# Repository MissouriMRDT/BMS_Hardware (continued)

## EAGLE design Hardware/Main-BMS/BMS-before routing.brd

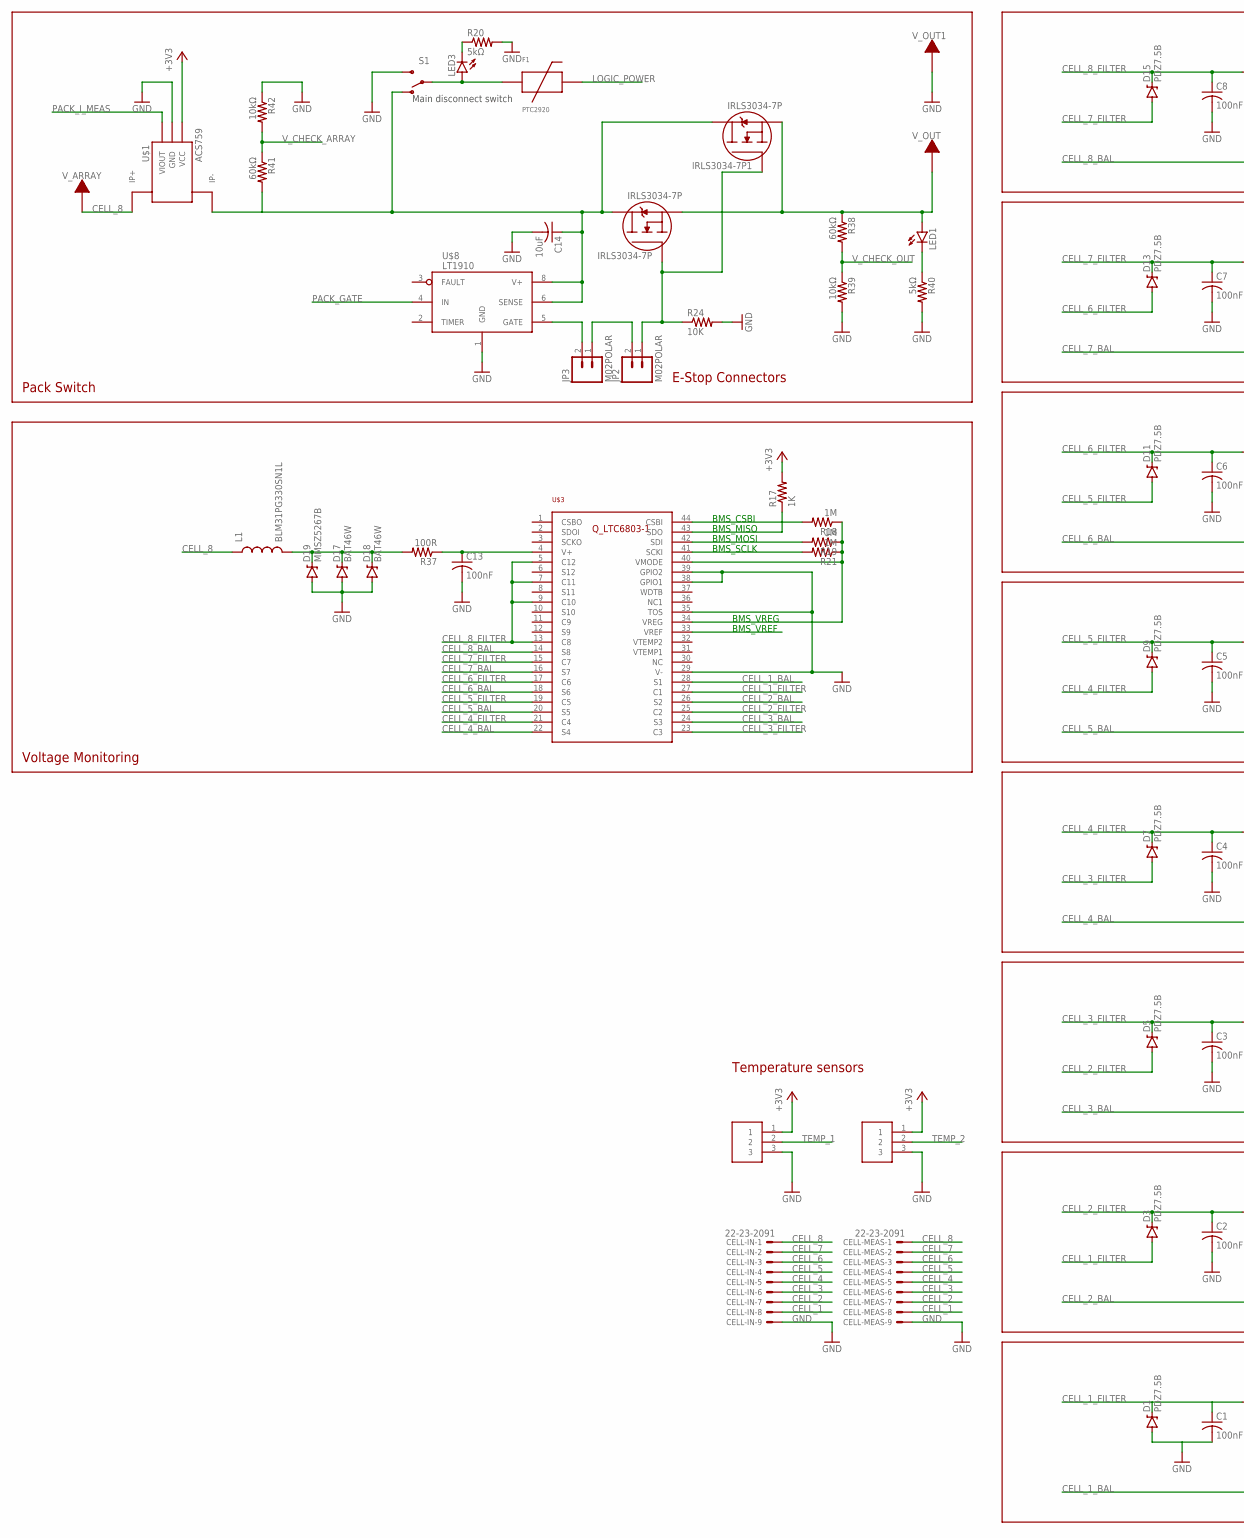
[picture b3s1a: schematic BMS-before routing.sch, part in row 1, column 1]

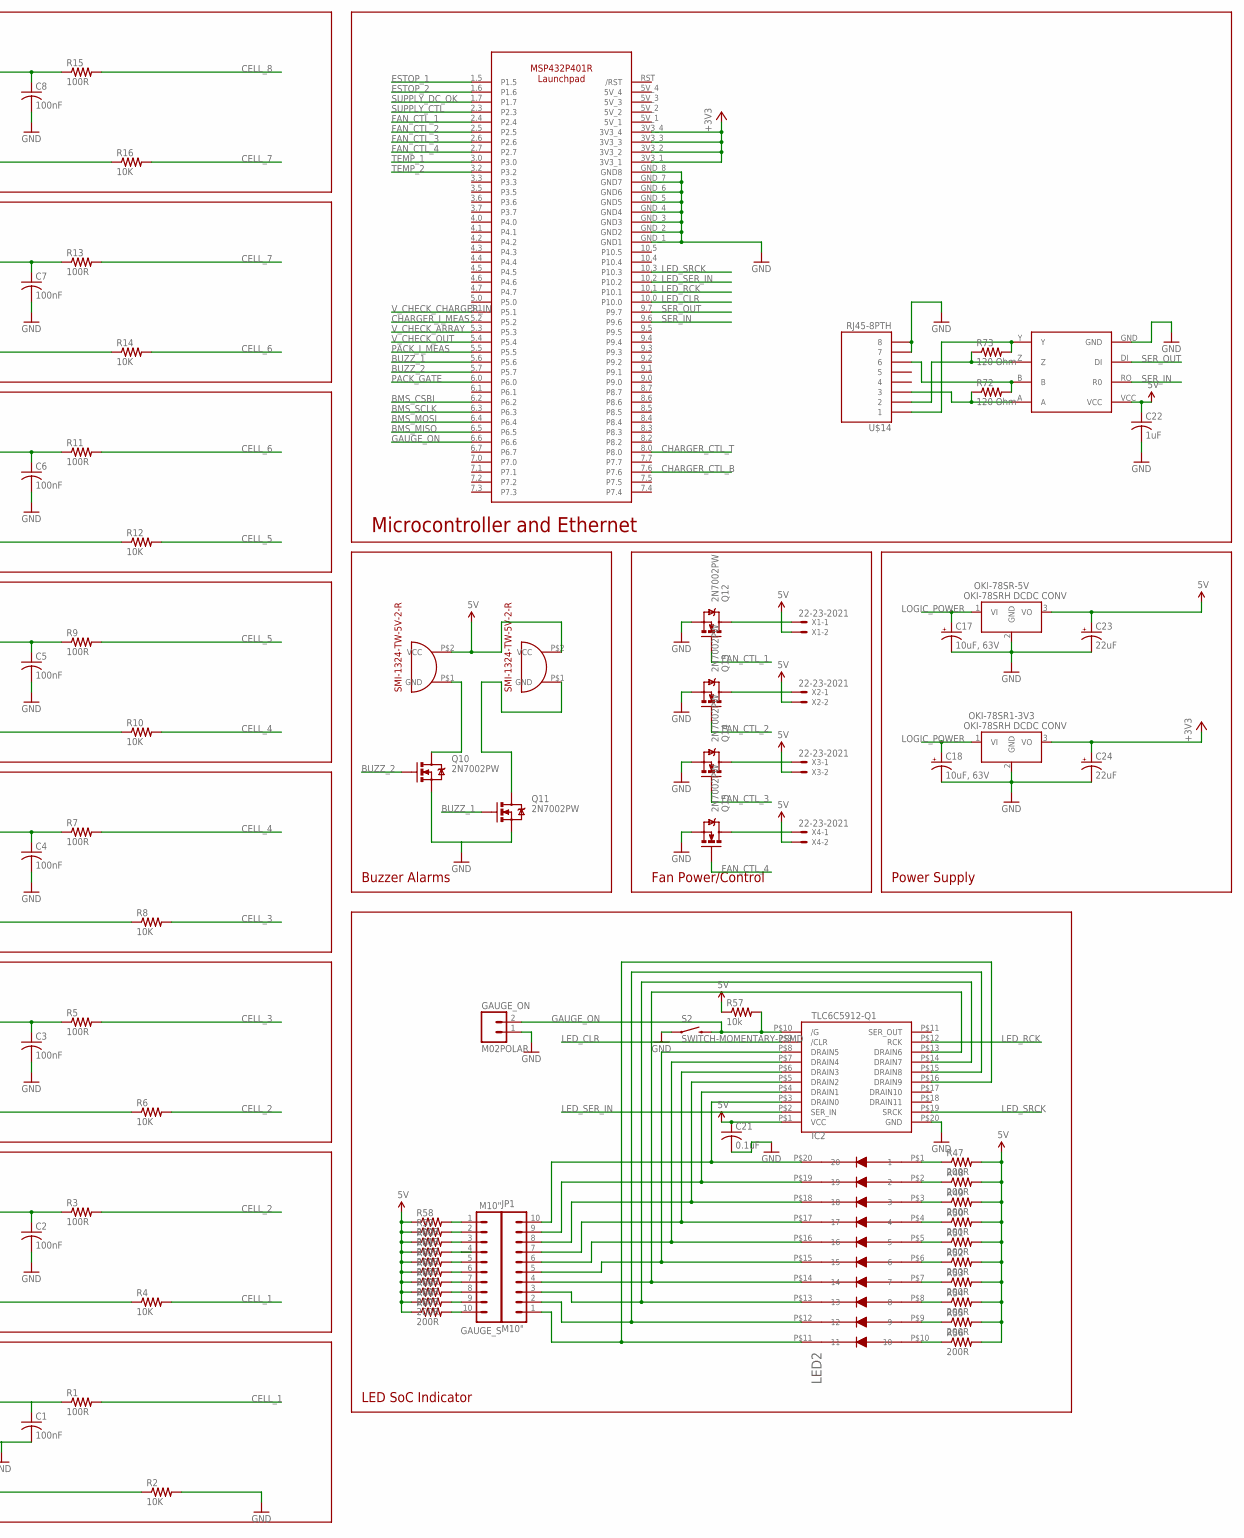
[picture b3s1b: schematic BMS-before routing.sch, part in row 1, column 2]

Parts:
C1, C2, C3, C4, C5, C6, C7, C8, C13: 100nF; C1206
C14: 10uF; C1206
C17, C18: 10uF, 63V; PANASONIC_D
C21: 0.1uF; C1206
C22: 1uF; C1206
C23, C24: 22uF; PANASONIC_D
CELL-IN: 22-23-2091
CELL-MEAS: 22-23-2091
D1, D3, D5, D7, D9, D11, D13, D15: PDZ7.5B; SOD-323
D17, D18: BAT46W; SOD-123
D19: MMSZ5267B; SOD-123
F1: PTC2920; 2920
GAUGE_ON: M02POLAR; MOLEX-1X2
GAUGE_S: M10"; 1X10
IC2: TLC6C5912-Q1; SOIC-20
IRLS3034-7P, IRLS3034-7P1: IRLS3034-7P; D2PAK-7
J1, J2: SL03THROUGH_HOLE; MOLEX_SL_03_THROUGH_HOLE
JP1: M10"; 1X10
JP2, JP3: M02POLAR; MOLEX-1X2
L1: BLM31PG330SN1L; 1210
LED1, LED3: LED1206; LED-1206
LED2: LED-DC7G3HWA; LED-10
OKI-78SR1-3V3: Q_OKI-78SR12; OKI-78SRH
OKI-78SR-5V: Q_OKI-78SR5; OKI-78SRH
Q10, Q11, Q12, Q13, Q14, Q15: 2N7002PW; SOT323
R1, R3, R5, R7, R9, R11, R13, R15, R37: 100R; R1206
R2, R4, R6, R8, R10, R12, R14, R16, R24: 10K; 0603-RES
R17: 1K; 0603-RES
R18, R19, R21: 1M; R1206
R20, R40: 5kΩ; R1206
R38, R41: 60kΩ; R1206
R39, R42: 10kΩ; R1206
R47, R48, R49, R50, R51, R52, R53, R54, R55, R56, R58, R59, R60, R61, R62, R63, R64, R65, R66, R67: 200R; R1206
R57: 10k; R1206
R72, R73: 120 Ohm; 1206
S1: SWITCH-SPDTPTH; SWITCH-SPDT
S2: SWITCH-MOMENTARY-2SMD; TACTILE-SWITCH-SMD
U$1: ACS759; PFF_LEADFORM
U$2, U$4: SMI-1324-TW-5V-2-R
U$3: Q_LTC6803-1; SSOP44
U$8: LT1910; SO8
U$13: MSP432P401R-LAUNCHPAD
U$14: RJ45-8PTH; RJ45-8
U$15: MAX3077; MAX3070E
V_ARRAY: TERMINAL_HOLE; LARGE_TERMINAL_HOLE
V_OUT, V_OUT1: TERMINAL_HOLE; LARGE_TERMINAL_HOLE
X1, X2, X3, X4: 22-23-2021

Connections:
5V: C21.1, C22.1, C23.+, IC2.P$1 (VCC), OKI-78SR-5V.3 (VO), R47.2, R48.2, R49.2, R50.2, R51.2, R52.2, R53.2, R54.2, R55.2, R56.2, R57.1, R58.1, R59.1, R60.1, R61.1, R62.1, R63.1, R64.1, R65.1, R66.1, R67.1, U$2.P$2 (VCC), U$4.P$2 (VCC), U$15.VCC, X1.2, X2.2, X3.2, X4.2
+3V3: C24.+, J1.1, J2.1, OKI-78SR1-3V3.3 (VO), R17.2, U$1.1 (VCC), U$13.3V3_1, U$13.3V3_2, U$13.3V3_3, U$13.3V3_4
BMS_CSBI: R18.2, U$3.44 (CSBI), U$13.6.2
BMS_MISO: R17.1, U$3.43 (SDO), U$13.6.5
BMS_MOSI: R19.2, U$3.42 (SDI), U$13.6.4
BMS_SCLK: R21.2, U$3.41 (SCKI), U$13.6.3
BMS_VREF: U$3.33 (VREF)
BMS_VREG: R18.1, R19.1, R21.1, U$3.34 (VREG), U$3.40 (VMODE)
BUZZ_1: Q11.1 (G), U$13.5.6
BUZZ_2: Q10.1 (G), U$13.5.7
CELL_1: CELL-IN.8, CELL-MEAS.8, R1.2, R4.2
CELL_1_BAL: R2.1, U$3.28 (S1)
CELL_1_FILTER: C1.1, D1.C, D3.A, R1.1, U$3.27 (C1)
CELL_2: CELL-IN.7, CELL-MEAS.7, R3.2, R6.2
CELL_2_BAL: R4.1, U$3.26 (S2)
CELL_2_FILTER: C2.1, D3.C, D5.A, R3.1, U$3.25 (C2)
CELL_3: CELL-IN.6, CELL-MEAS.6, R5.2, R8.2
CELL_3_BAL: R6.1, U$3.24 (S3)
CELL_3_FILTER: C3.1, D5.C, D7.A, R5.1, U$3.23 (C3)
CELL_4: CELL-IN.5, CELL-MEAS.5, R7.2, R10.2
CELL_4_BAL: R8.1, U$3.22 (S4)
CELL_4_FILTER: C4.1, D7.C, D9.A, R7.1, U$3.21 (C4)
CELL_5: CELL-IN.4, CELL-MEAS.4, R9.2, R12.2
CELL_5_BAL: R10.1, U$3.20 (S5)
CELL_5_FILTER: C5.1, D9.C, D11.A, R9.1, U$3.19 (C5)
CELL_6: CELL-IN.3, CELL-MEAS.3, R11.2, R14.2
CELL_6_BAL: R12.1, U$3.18 (S6)
CELL_6_FILTER: C6.1, D11.C, D13.A, R11.1, U$3.17 (C6)
CELL_7: CELL-IN.2, CELL-MEAS.2, R13.2, R16.2
CELL_7_BAL: R14.1, U$3.16 (S7)
CELL_7_FILTER: C7.1, D13.C, D15.A, R13.1, U$3.15 (C7)
CELL_8: CELL-IN.1, CELL-MEAS.1, L1.1, R15.2, U$1.4_1 (IP+), U$1.4_2 (IP+), U$1.4_3 (IP+), U$1.4_4 (IP+), U$1.4_5 (IP+), U$1.4_6 (IP+), U$1.4_7 (IP+), U$1.4_8 (IP+), U$1.4_9 (IP+), U$1.4_10 (IP+), U$1.4_11 (IP+), U$1.4_12 (IP+), U$1.4_13 (IP+), U$1.4_14 (IP+), U$1.4_15 (IP+), U$1.4_16 (IP+), U$1.4_B (IP+), V_ARRAY.P$1
CELL_8_BAL: R16.1, U$3.14 (S8)
CELL_8_FILTER: C8.1, D15.C, R15.1, U$3.5 (C12), U$3.7 (C11), U$3.9 (C10), U$3.13 (C8)
CHARGER_CTL_B: U$13.7.6
CHARGER_CTL_T: U$13.8.0
CHARGER_I_MEAS: U$13.5.2
ESTOP_1: U$13.1.5
ESTOP_2: U$13.1.6
FAN_CTL_1: Q12.1 (G), U$13.2.4
FAN_CTL_2: Q13.1 (G), U$13.2.5
FAN_CTL_3: Q14.1 (G), U$13.2.6
FAN_CTL_4: Q15.1 (G), U$13.2.7
GAUGE_D: IC2.P$6 (DRAIN3), JP1.7, LED2.P$17 (17)
GAUGE_ON: GAUGE_ON.2, IC2.P$10 (/G), R57.2, S2.3 (2), U$13.6.6
GND: C1.2, C2.2, C3.2, C4.2, C5.2, C6.2, C7.2, C8.2, C13.2, C14.2, C17.-, C18.-, C21.2, C22.2, C23.-, C24.-, CELL-IN.9, CELL-MEAS.9, D1.A, D17.A, D18.A, D19.A, GAUGE_ON.1, IC2.P$20 (GND), J1.3, J2.3, OKI-78SR1-3V3.2 (GND), OKI-78SR-5V.2 (GND), Q10.2 (S), Q11.2 (S), Q12.2 (S), Q13.2 (S), Q14.2 (S), Q15.2 (S), R2.2, R20.2, R24.2, R39.2, R40.2, R42.1, S1.3 (S), S2.1, U$1.2 (GND), U$3.29 (V-), U$3.35 (TOS), U$3.38 (GPIO1), U$3.39 (GPIO2), U$8.1 (GND), U$13.GND_1 (GND1), U$13.GND_2 (GND2), U$13.GND_3 (GND3), U$13.GND_4 (GND4), U$13.GND_5 (GND5), U$13.GND_6 (GND6), U$13.GND_7 (GND7), U$13.GND_8 (GND8), U$14.7, U$14.8, U$15.GND, V_OUT1.P$1
LED_CLR: IC2.P$9 (/CLR), U$13.10.0
LED_RCK: IC2.P$12 (RCK), U$13.10.1
LED_SER_IN: IC2.P$2 (SER_IN), U$13.10.2
LED_SRCK: IC2.P$19 (SRCK), U$13.10.3
LOGIC_POWER: C17.+, C18.+, F1.P$2, OKI-78SR1-3V3.1 (VI), OKI-78SR-5V.1 (VI)
unnamed: JP3.2, U$8.5 (GATE)
unnamed: F1.P$1, LED3.A, S1.2
unnamed: IRLS3034-7P.2 (SOURCE), IRLS3034-7P.3 (SOURCE), IRLS3034-7P.4 (SOURCE), IRLS3034-7P.5 (SOURCE), IRLS3034-7P.6 (SOURCE), IRLS3034-7P1.2 (SOURCE), IRLS3034-7P1.3 (SOURCE), IRLS3034-7P1.4 (SOURCE), IRLS3034-7P1.5 (SOURCE), IRLS3034-7P1.6 (SOURCE), LED1.A, R38.1, V_OUT.P$1
unnamed: LED3.C, R20.1
unnamed: JP2.2, JP3.1
unnamed: D17.C, D18.C, D19.C, L1.2, R37.2
unnamed: C13.1, R37.1, U$3.4 (V+)
unnamed: IC2.P$3 (DRAIN0), JP1.10, LED2.P$20 (20)
unnamed: IRLS3034-7P.1 (GATE), IRLS3034-7P1.1 (GATE), JP2.1, R24.1
unnamed: R73.2, U$14.1, U$15.Y
unnamed: LED1.C, R40.1
unnamed: C14.1, IRLS3034-7P.PAD (DRAIN), IRLS3034-7P1.PAD (DRAIN), R41.2, S1.1 (O), U$1.5_1 (IP-), U$1.5_2 (IP-), U$1.5_3 (IP-), U$1.5_4 (IP-), U$1.5_5 (IP-), U$1.5_6 (IP-), U$1.5_7 (IP-), U$1.5_8 (IP-), U$1.5_9 (IP-), U$1.5_10 (IP-), U$1.5_11 (IP-), U$1.5_12 (IP-), U$1.5_13 (IP-), U$1.5_14 (IP-), U$1.5_15 (IP-), U$1.5_16 (IP-), U$1.5_B (IP-), U$1.5_T (IP-), U$8.6 (SENSE), U$8.8 (V+)
unnamed: IC2.P$4 (DRAIN1), JP1.9, LED2.P$19 (19)
unnamed: IC2.P$5 (DRAIN2), JP1.8, LED2.P$18 (18)
unnamed: R73.1, U$14.2, U$15.Z
unnamed: IC2.P$7 (DRAIN4), JP1.6, LED2.P$16 (16)
unnamed: IC2.P$8 (DRAIN5), JP1.5, LED2.P$15 (15)
unnamed: IC2.P$13 (DRAIN6), JP1.4, LED2.P$14 (14)
unnamed: IC2.P$14 (DRAIN7), JP1.3, LED2.P$13 (13)
unnamed: IC2.P$15 (DRAIN8), JP1.2, LED2.P$12 (12)
unnamed: IC2.P$16 (DRAIN9), JP1.1, LED2.P$11 (11)
unnamed: LED2.P$1 (1), R47.1
unnamed: LED2.P$2 (2), R48.1
unnamed: LED2.P$3 (3), R49.1
unnamed: LED2.P$4 (4), R50.1
unnamed: LED2.P$5 (5), R51.1
unnamed: LED2.P$6 (6), R52.1
unnamed: LED2.P$7 (7), R53.1
unnamed: LED2.P$8 (8), R54.1
unnamed: LED2.P$9 (9), R55.1
unnamed: LED2.P$10 (10), R56.1
unnamed: R72.2, U$14.6, U$15.B
unnamed: Q11.3 (D), U$4.P$1 (GND)
unnamed: Q10.3 (D), U$2.P$1 (GND)
unnamed: Q12.3 (D), X1.1
unnamed: R72.1, U$14.3, U$15.A
unnamed: Q13.3 (D), X2.1
unnamed: Q14.3 (D), X3.1
unnamed: Q15.3 (D), X4.1
unnamed: GAUGE_S.1, R58.2
unnamed: GAUGE_S.2, R59.2
unnamed: GAUGE_S.3, R60.2
unnamed: GAUGE_S.4, R61.2
unnamed: GAUGE_S.5, R62.2
unnamed: GAUGE_S.6, R63.2
unnamed: GAUGE_S.7, R64.2
unnamed: GAUGE_S.8, R65.2
unnamed: GAUGE_S.9, R66.2
unnamed: GAUGE_S.10, R67.2
PACK_GATE: U$8.4 (IN), U$13.6.0
PACK_I_MEAS: U$1.3 (VIOUT), U$13.5.5
SER_IN: U$13.9.6, U$15.RO (R0)
SER_OUT: U$13.9.7, U$15.DI
SUPPLY_CTL: U$13.2.3
SUPPLY_DC_OK: U$13.1.7
TEMP_1: J2.2, U$13.3.0
TEMP_2: J1.2, U$13.3.2
V_CHECK_ARRAY: R41.1, R42.2, U$13.5.3
V_CHECK_CHARGER_IN: U$13.5.1
V_CHECK_OUT: R38.2, R39.1, U$13.5.4

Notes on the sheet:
Pack Switch
Main disconnect switch
E-Stop Connectors
Power Supply
LED SoC Indicator
Buzzer Alarms
Fan Power/Control
Microcontroller and Ethernet
CELL_8_FILTER
CELL_7_FILTER
CELL_6_FILTER
CELL_5_FILTER
CELL_4_FILTER
CELL_4_BAL
CELL_5_BAL
CELL_6_BAL
CELL_7_BAL
CELL_8_BAL
CELL_1_BAL
CELL_1_FILTER
CELL_1
CELL_2_BAL
CELL_3_FILTER
CELL_2_FILTER
CELL_3_BAL
BMS_VREG
BMS_VREF
BMS_CSBI
BMS_MISO
BMS_MOSI
BMS_SCLK
Voltage Monitoring
Temperature sensors

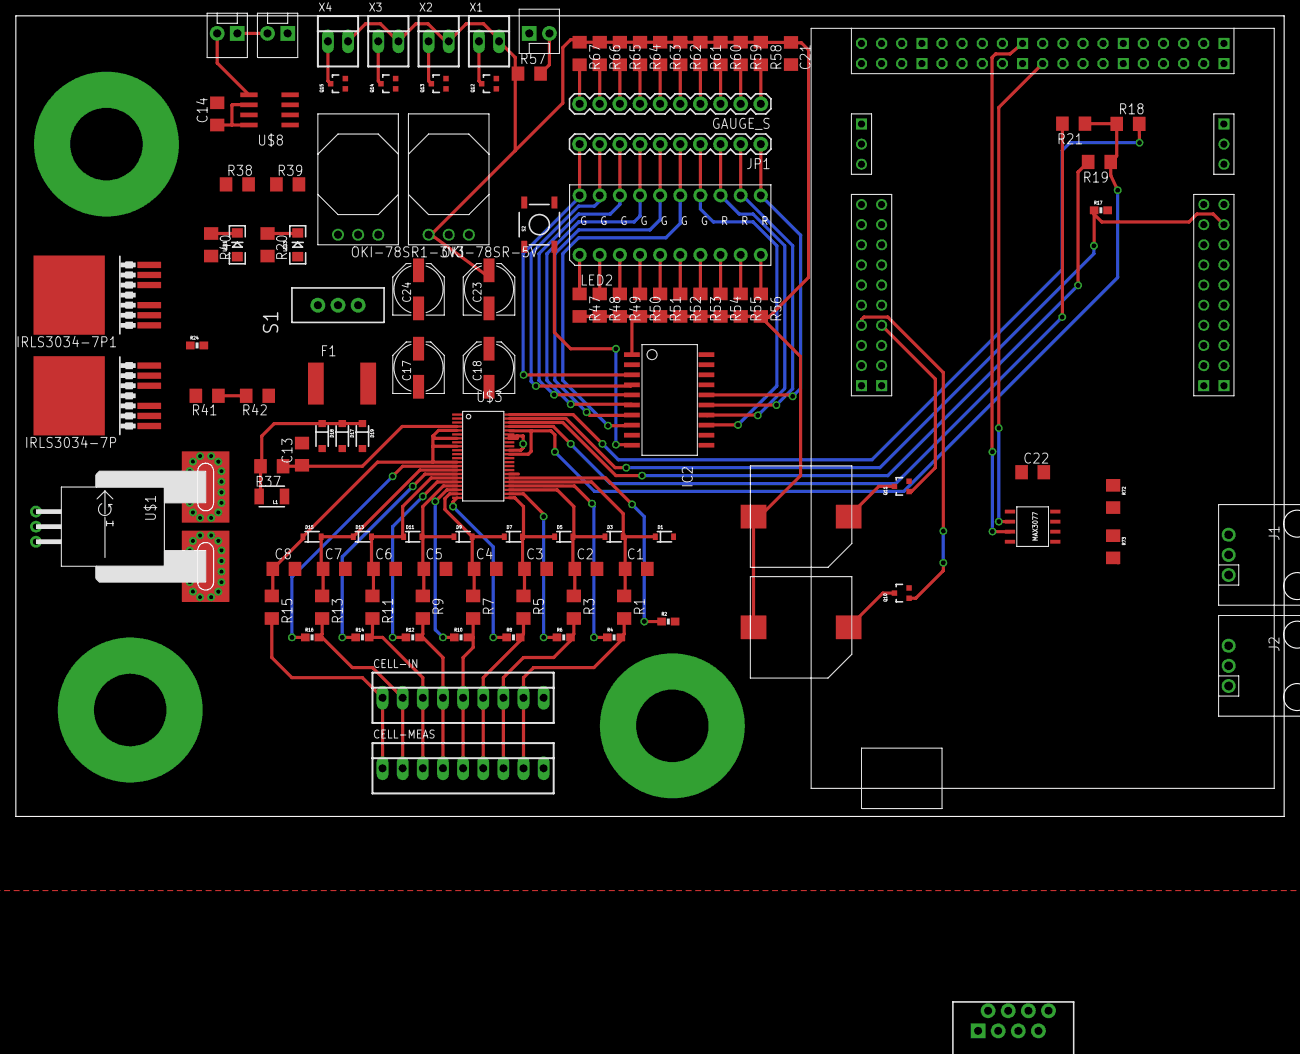
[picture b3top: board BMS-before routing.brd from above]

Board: 2 copper layers, 160.0 x 101.0 mm, 120 parts (0 on the bottom side), 102 nets.

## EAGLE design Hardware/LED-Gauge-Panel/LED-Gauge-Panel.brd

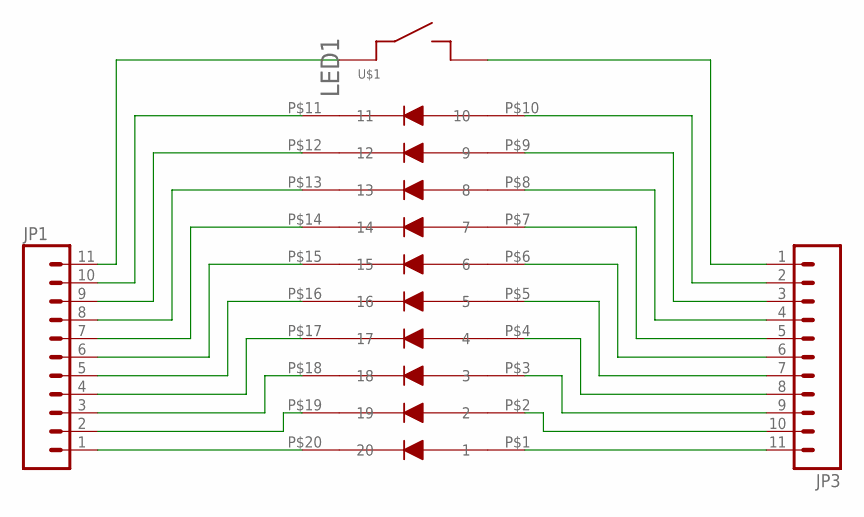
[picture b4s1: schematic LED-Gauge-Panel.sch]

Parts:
JP1, JP3: M11PTH; 1X11
LED1: LED-DC7G3HWA; LED-10
U$1: MOMENTARY-SWITCH-EVQ1; EVQ11

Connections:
unnamed: JP1.1, LED1.P$20 (20)
unnamed: JP1.2, LED1.P$19 (19)
unnamed: JP1.3, LED1.P$18 (18)
unnamed: JP1.4, LED1.P$17 (17)
unnamed: JP1.5, LED1.P$16 (16)
unnamed: JP1.6, LED1.P$15 (15)
unnamed: JP1.7, LED1.P$14 (14)
unnamed: JP1.8, LED1.P$13 (13)
unnamed: JP1.9, LED1.P$12 (12)
unnamed: JP1.10, LED1.P$11 (11)
unnamed: JP3.11, LED1.P$1 (1)
unnamed: JP3.10, LED1.P$2 (2)
unnamed: JP3.9, LED1.P$3 (3)
unnamed: JP3.8, LED1.P$4 (4)
unnamed: JP3.7, LED1.P$5 (5)
unnamed: JP3.6, LED1.P$6 (6)
unnamed: JP3.5, LED1.P$7 (7)
unnamed: JP3.4, LED1.P$8 (8)
unnamed: JP3.3, LED1.P$9 (9)
unnamed: JP3.2, LED1.P$10 (10)
unnamed: JP1.11, U$1.P$1
unnamed: JP3.1, U$1.P$2

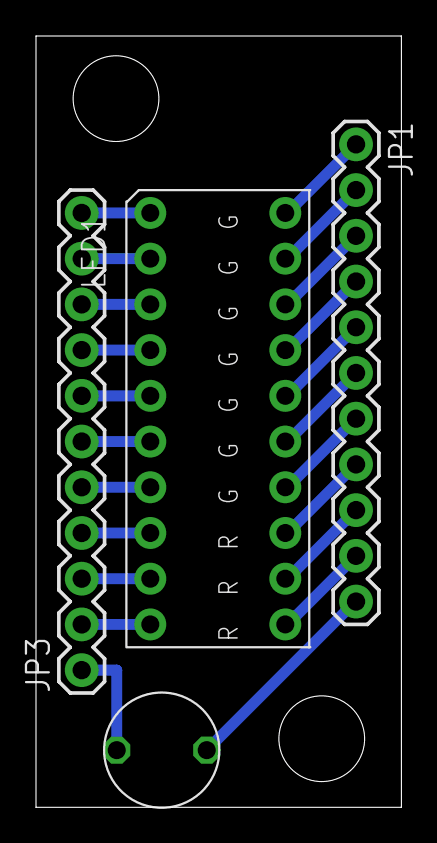
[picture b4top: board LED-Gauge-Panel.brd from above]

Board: 2 copper layers, 20.3 x 42.9 mm, 4 parts (0 on the bottom side), 22 nets.

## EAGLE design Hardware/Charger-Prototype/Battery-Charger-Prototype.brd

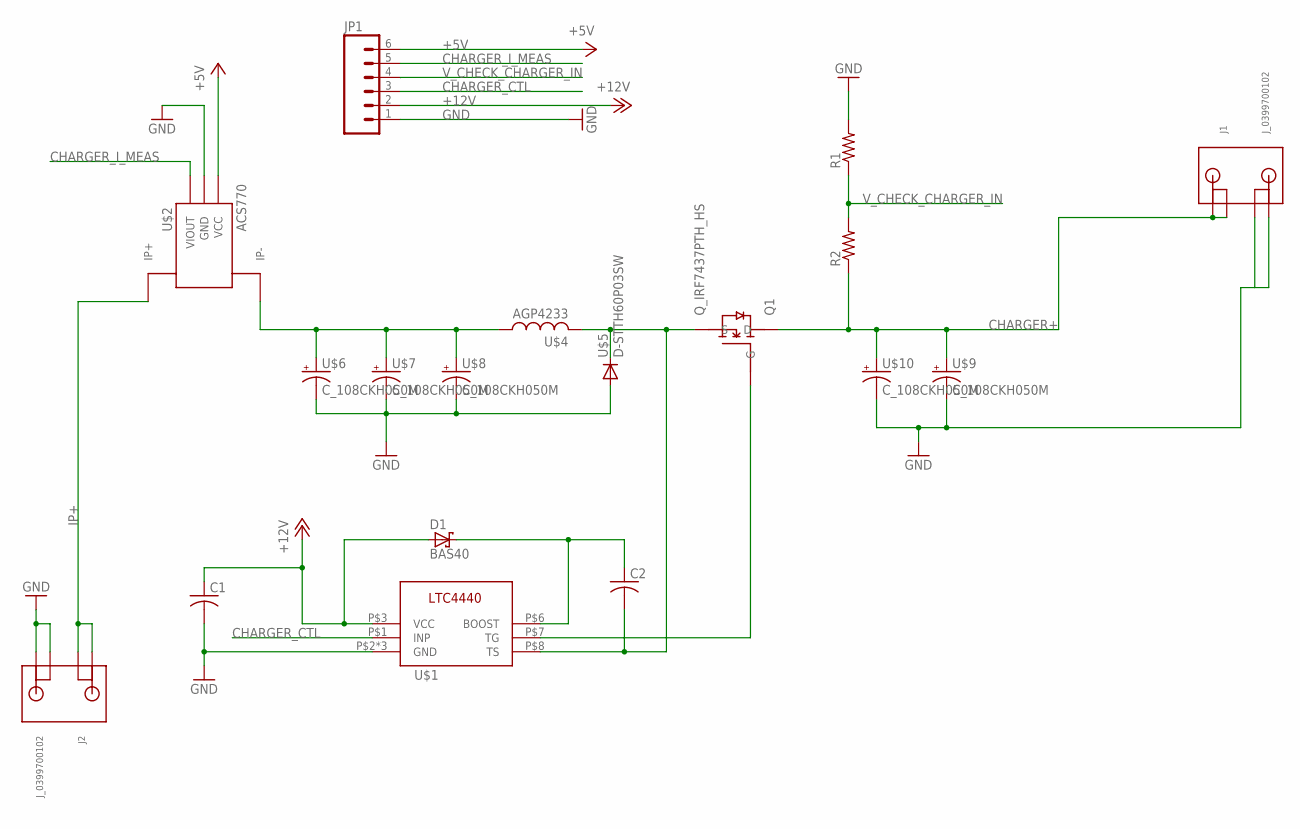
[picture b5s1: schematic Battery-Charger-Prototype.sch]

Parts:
C1, C2: C-USC1206; C1206
D1: BAS40; SOT23
J1, J2: J_0399700102; J_2CONHC
JP1: M06SILK_FEMALE_PTH; 1X06
Q1: Q_IRF7437PTH_HS; TO-220-531102B02500G
R1, R2: R-US_R1206; R1206
U$1: LTC4440; MS8E
U$2: ACS770; PFF_LEADFORM
U$4: AGP4233
U$5: D-STTH60P03SW; TO-247-VERT
U$6, U$7, U$8, U$9, U$10: C_108CKH050M; C_16MM

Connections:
+5V: JP1.6, U$2.1 (VCC)
+12V: C1.1, D1.1 (A), JP1.2, U$1.P$3 (VCC)
CHARGER+: J1.PIN1-1 (1-1), J1.PIN1-2 (1-2), Q1.2 (D), R2.1, U$9.+, U$10.+
CHARGER_CTL: JP1.3, U$1.P$1 (INP)
CHARGER_I_MEAS: JP1.5, U$2.3 (VIOUT)
GND: C1.2, J1.PIN2-1 (2-1), J1.PIN2-2 (2-2), J2.PIN2-1 (2-1), J2.PIN2-2 (2-2), JP1.1, R1.2, U$1.P$2 (GND), U$1.P$4 (GND), U$1.P$9 (GND), U$2.2 (GND), U$5.P$1 (A), U$5.P$3 (A), U$6.GND (-), U$7.GND (-), U$8.GND (-), U$9.GND (-), U$10.GND (-)
IP+: J2.PIN1-1 (1-1), J2.PIN1-2 (1-2), U$2.4_1 (IP+), U$2.4_2 (IP+), U$2.4_3 (IP+), U$2.4_4 (IP+), U$2.4_5 (IP+), U$2.4_6 (IP+), U$2.4_7 (IP+), U$2.4_8 (IP+), U$2.4_9 (IP+), U$2.4_10 (IP+), U$2.4_11 (IP+), U$2.4_12 (IP+), U$2.4_13 (IP+), U$2.4_14 (IP+), U$2.4_15 (IP+), U$2.4_16 (IP+), U$2.4_B (IP+), U$2.4_T (IP+)
IP-: U$2.5_1 (IP-), U$2.5_2 (IP-), U$2.5_3 (IP-), U$2.5_4 (IP-), U$2.5_5 (IP-), U$2.5_6 (IP-), U$2.5_7 (IP-), U$2.5_8 (IP-), U$2.5_9 (IP-), U$2.5_10 (IP-), U$2.5_11 (IP-), U$2.5_12 (IP-), U$2.5_13 (IP-), U$2.5_14 (IP-), U$2.5_15 (IP-), U$2.5_16 (IP-), U$2.5_B (IP-), U$2.5_T (IP-), U$4.P$1 (1), U$6.+, U$7.+, U$8.+
MOS_OUT: C2.2, Q1.3 (S), U$1.P$8 (TS), U$4.P$2 (2), U$5.P$2 (C)
unnamed: C2.1, D1.3 (C), U$1.P$6 (BOOST)
unnamed: Q1.1 (G), U$1.P$7 (TG)
V_CHECK_CHARGER_IN: JP1.4, R1.1, R2.2

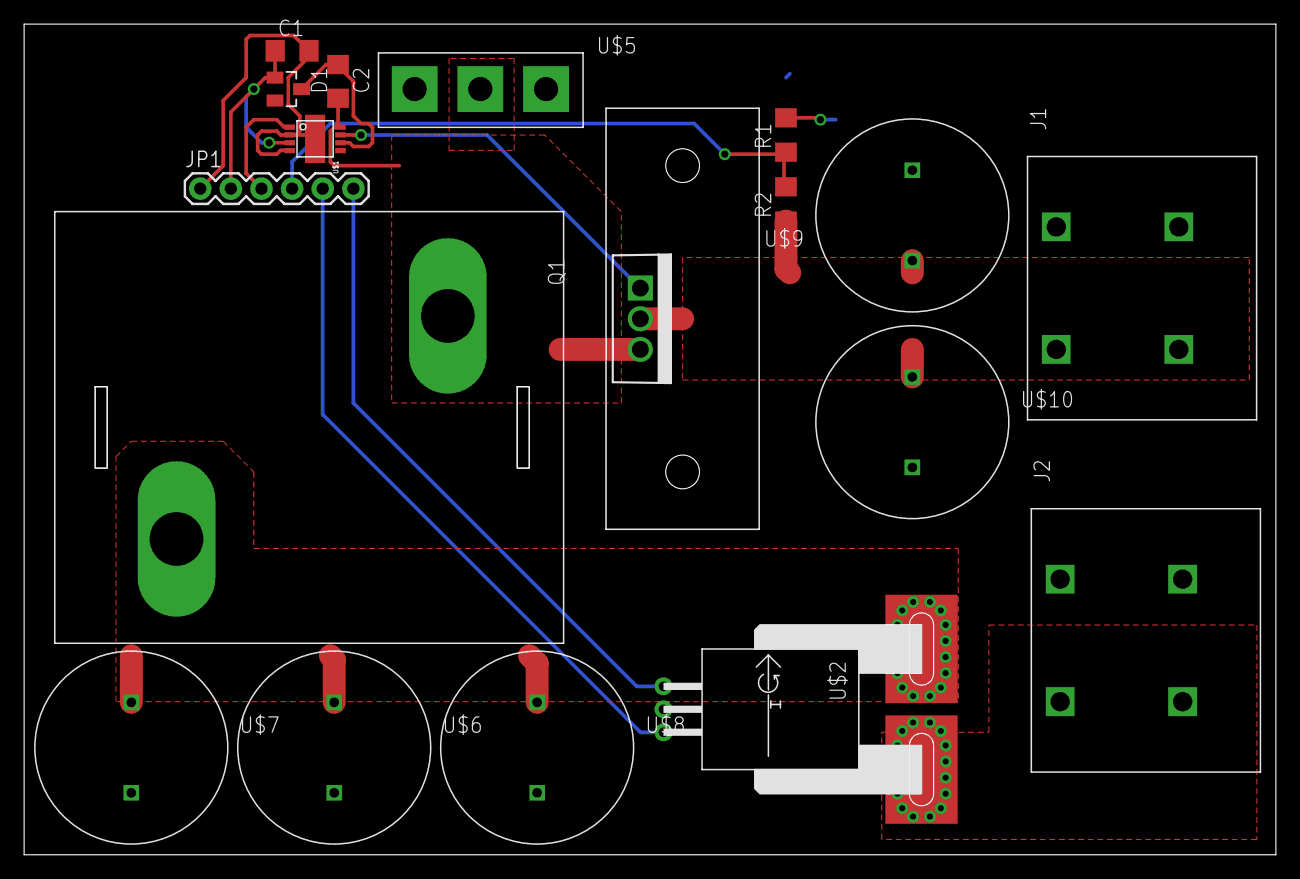
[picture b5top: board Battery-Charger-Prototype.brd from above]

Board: 2 copper layers, 103.8 x 68.9 mm, 18 parts (0 on the bottom side), 12 nets.
